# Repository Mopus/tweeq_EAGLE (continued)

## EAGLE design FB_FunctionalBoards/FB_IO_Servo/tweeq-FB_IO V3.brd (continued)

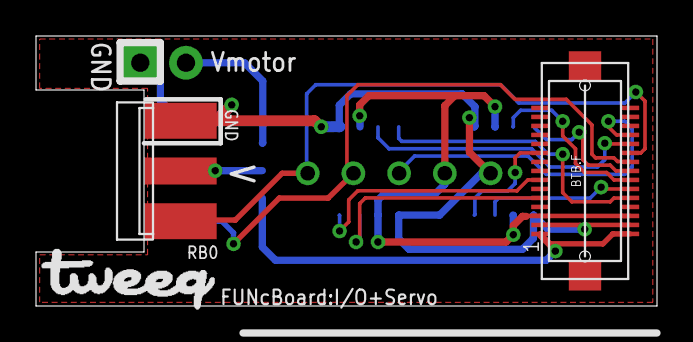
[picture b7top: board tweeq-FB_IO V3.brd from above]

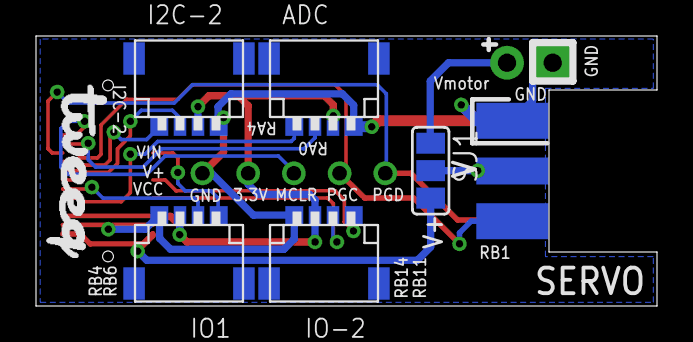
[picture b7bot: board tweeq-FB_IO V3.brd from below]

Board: 2 copper layers, 34.5 x 15.0 mm, 11 parts (6 on the bottom side), 16 nets.

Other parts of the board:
U$2, U$3: TWEEQ-LOGO-M

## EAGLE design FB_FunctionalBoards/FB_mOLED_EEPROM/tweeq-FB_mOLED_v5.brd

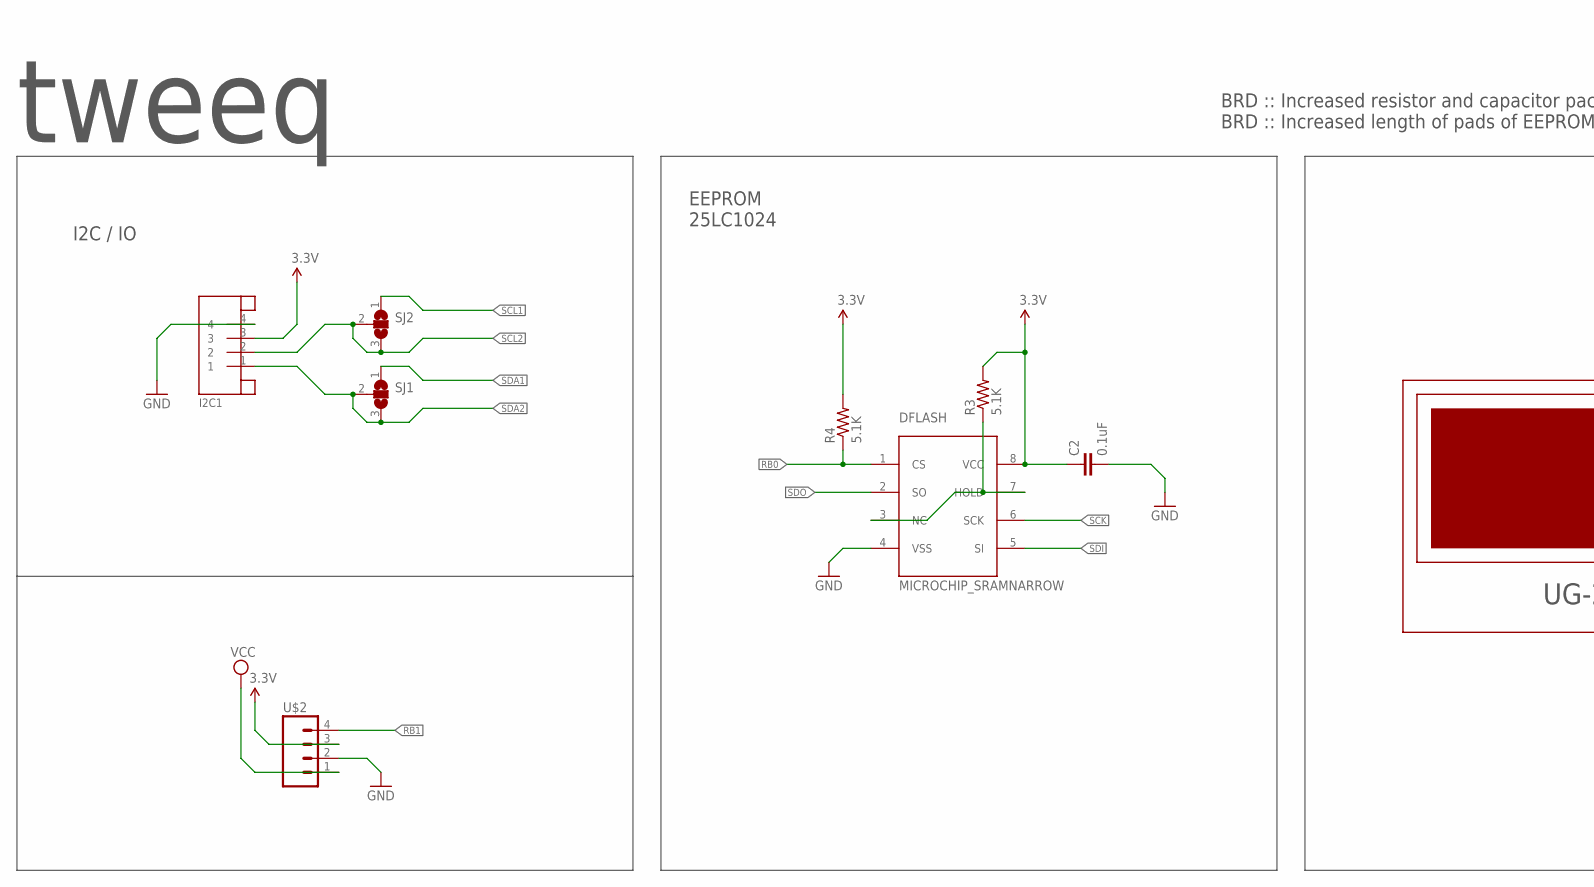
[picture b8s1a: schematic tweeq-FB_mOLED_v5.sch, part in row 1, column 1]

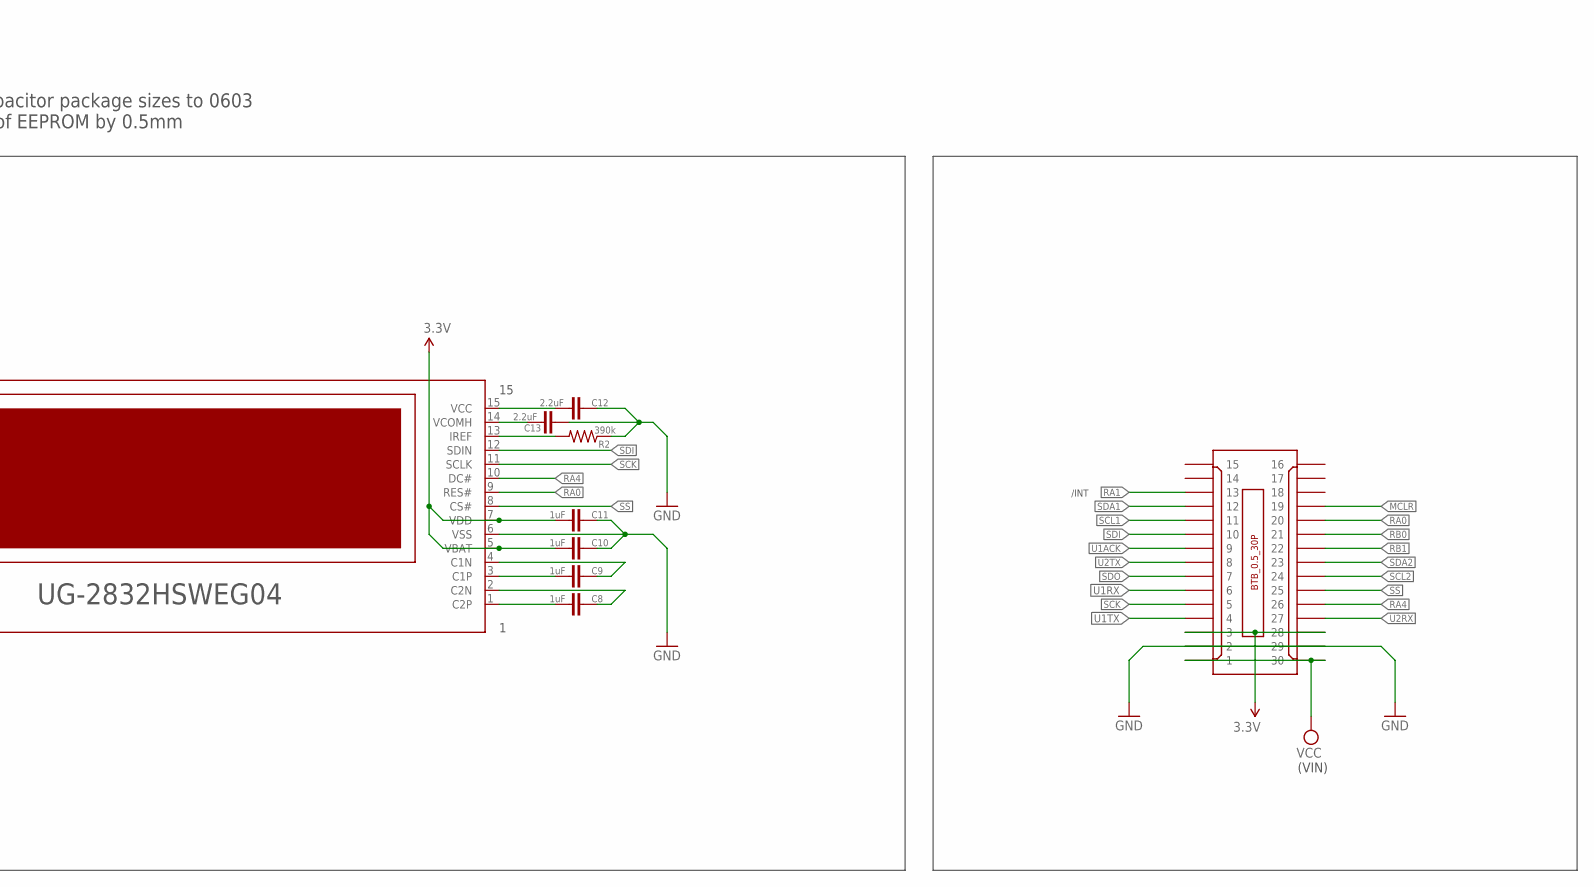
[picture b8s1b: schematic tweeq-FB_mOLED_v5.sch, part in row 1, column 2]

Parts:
C2: 0.1uF; C0603
C8, C9, C10, C11: 1uF; C0603K
C12, C13: 2.2uF; C0603K
DFLASH: MICROCHIP_SRAMNARROW; SOIC8
I2C1: JST-4PINSH; SH1.0-4PIN
R2: 390k; R0603
R3, R4: 5.1K; R0603
SJ1, SJ2: JUMPER_SJ2WS; JUMPER_SJ_S
U$2: M04; 1X04_PAD
U$3: UG-2832HSWEG04
U$4: BTB_CONN_30P/F; BTB0.5-30F-3.0G

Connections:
3.3V: C2.1, C10.1, C11.1, DFLASH.8 (VCC), I2C1.3, R3.2, R4.2, U$2.3, U$3.5 (VBAT), U$3.7 (VDD), U$4.3, U$4.28
GND: C2.2, C10.2, C11.2, C12.2, C13.2, DFLASH.4 (VSS), I2C1.4, R2.1, U$2.2, U$3.6 (VSS), U$4.2, U$4.29
MCLR: U$4.19
unnamed: C8.1, U$3.1 (C2P)
unnamed: C8.2, U$3.2 (C2N)
unnamed: DFLASH.3 (NC), DFLASH.7 (HOLD), R3.1
unnamed: C9.1, U$3.3 (C1P)
unnamed: C9.2, U$3.4 (C1N)
unnamed: C12.1, U$3.15 (VCC)
unnamed: C13.1, U$3.14 (VCOMH)
unnamed: R2.2, U$3.13 (IREF)
RA0: U$3.9 (RES#), U$4.20
RA1: U$4.13
RA4: U$3.10 (DC#), U$4.26
RB0: DFLASH.1 (CS), R4.1, U$4.21
RB1: U$2.4, U$4.22
SCK: DFLASH.6 (SCK), U$3.11 (SCLK), U$4.5
SCL1: SJ2.1, U$4.11
SCL2: I2C1.2, SJ2.2, SJ2.3, U$4.24
SDA1: SJ1.1, U$4.12
SDA2: I2C1.1, SJ1.2, SJ1.3, U$4.23
SDI: DFLASH.5 (SI), U$3.12 (SDIN), U$4.10
SDO: DFLASH.2 (SO), U$4.7
SS: U$3.8 (CS#), U$4.25
U1ACK: U$4.9
U1RX: U$4.6
U1TX: U$4.4
U2RX: U$4.27
U2TX: U$4.8
VCC: U$2.1, U$4.1, U$4.30

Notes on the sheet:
tweeq
EEPROM 25LC1024
(VIN)
/INT
I2C / IO
BRD :: Increased resistor and capacitor package sizes to 0603 BRD :: Increased length of pads of EEPROM by 0.5mm

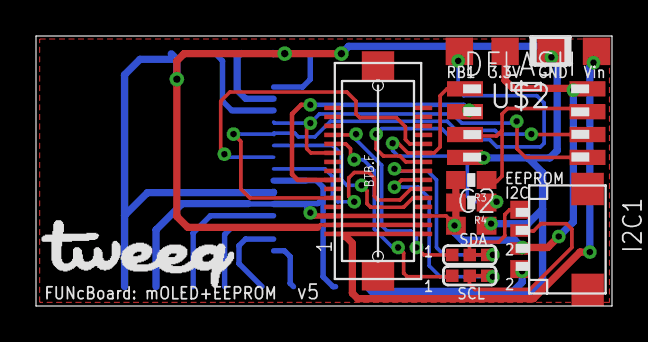
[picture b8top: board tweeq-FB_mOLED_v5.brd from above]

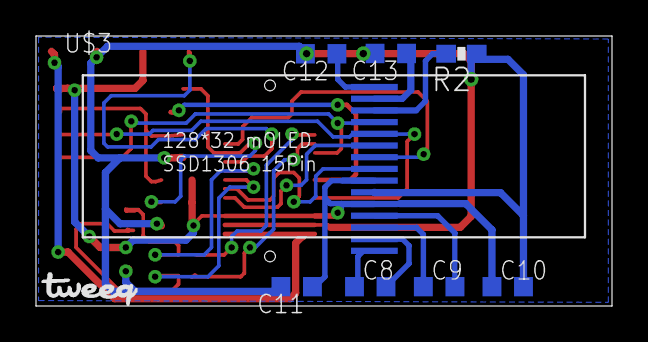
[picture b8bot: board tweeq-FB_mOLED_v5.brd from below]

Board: 2 copper layers, 32.0 x 15.0 mm, 19 parts (9 on the bottom side), 23 nets.

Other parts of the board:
U$5: TWEEQ-LOGO-L
U$6: TWEEQ-LOGO-S
